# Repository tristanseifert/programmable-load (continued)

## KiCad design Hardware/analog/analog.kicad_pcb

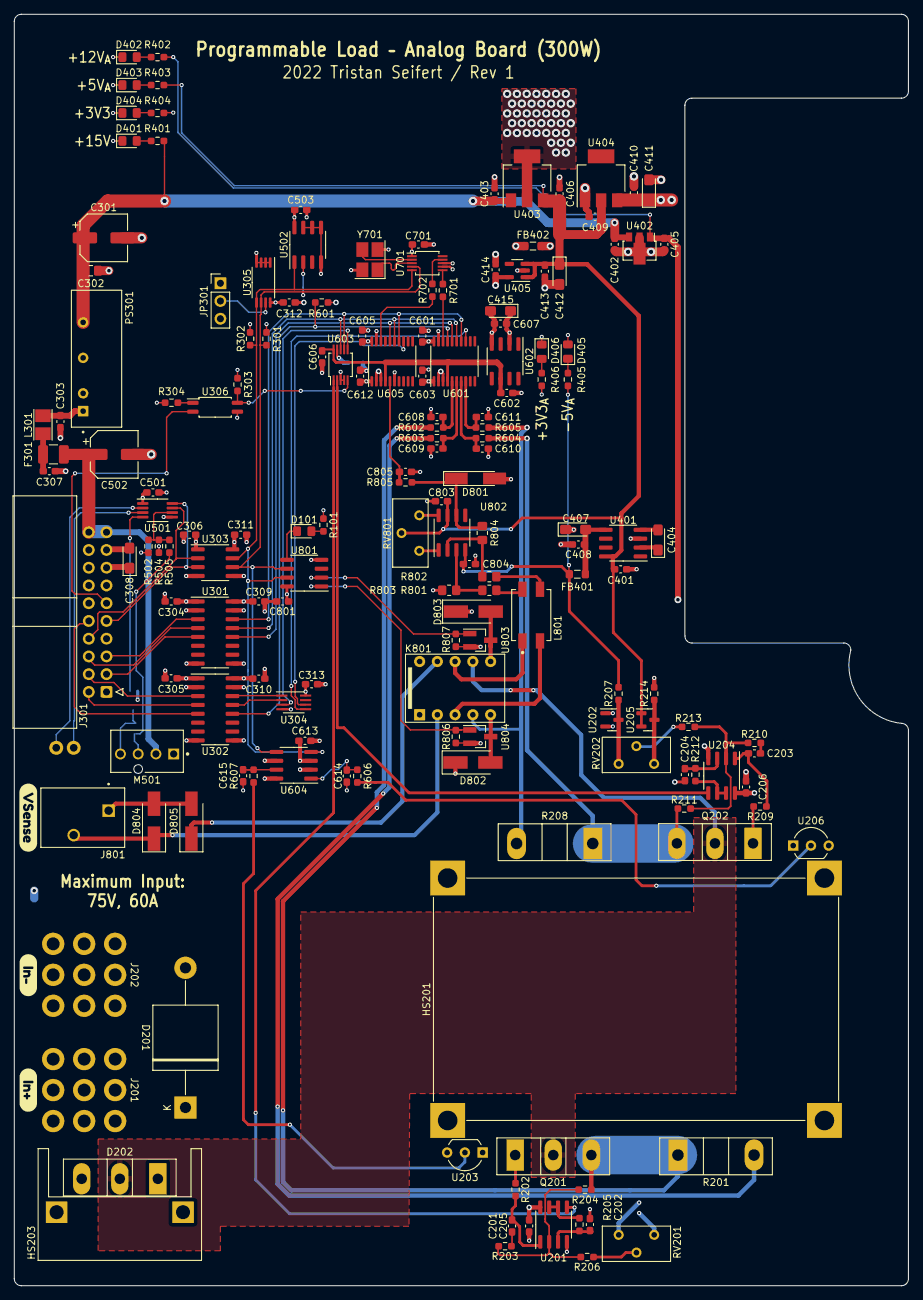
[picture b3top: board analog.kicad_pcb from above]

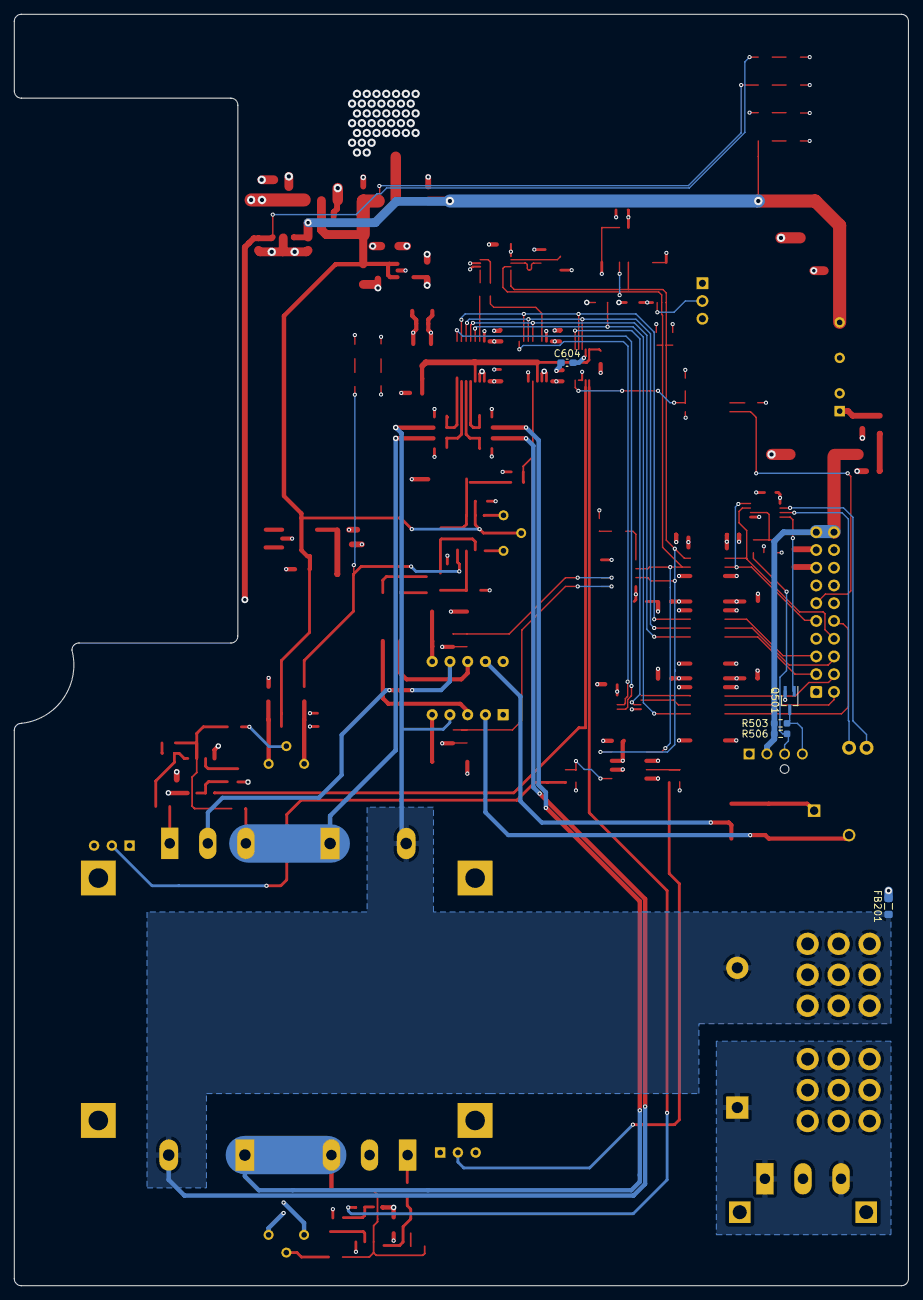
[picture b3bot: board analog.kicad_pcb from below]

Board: 4 copper layers, 128.0 x 182.0 mm, 174 parts (5 on the bottom side), 108 nets.

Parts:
C201, C203: 1nF; C_0603_1608Metric_Pad1.08x0.95mm_HandSolder
C202, C204: 22nF; C_0603_1608Metric_Pad1.08x0.95mm_HandSolder
C205, C206, C304, C305, C306, C309, C310, C311, C312, C313, C408, C501, C503, C601, C603, C604, C605, C607, C608, C609, C610, C611, C612, C613, C614, C615, C701, C801, C803, C804, C805: 100nF; C_0603_1608Metric_Pad1.08x0.95mm_HandSolder
C301, C502: 33µF; CP_Elec_6.3x5.7
C302: 10µF; C_0805_2012Metric_Pad1.18x1.45mm_HandSolder
C303, C307, C401, C402, C403, C405, C406, C409, C410, C413, C414, C602, C606: 4.7µF; C_0603_1608Metric_Pad1.08x0.95mm_HandSolder
C308, C404, C407, C411, C412, C415: 10µF; CP_EIA-3216-18_Kemet-A_Pad1.58x1.35mm_HandSolder
D101: Red; LED_0805_2012Metric_Pad1.15x1.40mm_HandSolder
D201: 5KP78A; D_P600_R-6_P20.00mm_Horizontal
D202: DSA120C150QB; TO-247-3_Vertical
D401, D402, D403, D404, D405, D406: Green; LED_0805_2012Metric_Pad1.15x1.40mm_HandSolder
D801: 2V4; D_MiniMELF_Handsoldering
D802, D803: SM4007; D_SMA_Handsoldering
D804: 75V; D_SMA_Handsoldering
D805: SS110; D_SMA_Handsoldering
F301: 350mA; Fuse_1210_3225Metric_Pad1.42x2.65mm_HandSolder
FB201, FB401, FB402: FerriteBead_Small; L_0805_2012Metric_Pad1.05x1.20mm_HandSolder
HS201: 2x C40-058-AE; C40-058-AE-DUAL
HS203: WV-T247-101E; Ohmite-WA-T247-101E-MFG
J201, J202: Würth 74651194R; WE-74651194
J301: Conn_02x10_Odd_Even; IDC-Header_2x10_P2.54mm_Horizontal
J501, J502: Conn_01x01; MillMax-2108-2
J801: Conn_01x02; CUI_TBL002A-350-02GR-2OR
JP301: Cfg WP; PinHeader_1x03_P2.54mm_Vertical
K801: EA2-3T; KEMET-EA2
L301: 6.8µH; L_Taiyo-Yuden_NR-24xx_HandSoldering
L801: L_Ferrite_Coupled_1423; Bourns-DR331-0-0-MFG
M501: Fan_4pin; Molex-47053-1000-MFG
PS301: PCN2-S12-S15-S; CONV_PCN2-S12-S15-S
Q201, Q202: IXTH80N075L2; TO-247-3_Vertical
Q501: MMBT3904; SOT-323_SC-70_Handsoldering
R101, R203, R204, R207, R210, R211, R214, R404, R406, R602, R603, R604, R605: 1k; R_0603_1608Metric_Pad0.98x0.95mm_HandSolder
R201, R208: .05R; TO-247-2_Vertical
R202, R209: 100R; R_0603_1608Metric_Pad0.98x0.95mm_HandSolder
R205, R212, R402, R805: 4k99; R_0603_1608Metric_Pad0.98x0.95mm_HandSolder
R206, R213: 330k (?); R_0603_1608Metric_Pad0.98x0.95mm_HandSolder
R301, R302, R403, R405: 2k2; R_0603_1608Metric_Pad0.98x0.95mm_HandSolder
R303, R504, R601: 10k; R_0603_1608Metric_Pad0.98x0.95mm_HandSolder
R304: 200R; R_0603_1608Metric_Pad0.98x0.95mm_HandSolder
R401: 7k5; R_0603_1608Metric_Pad0.98x0.95mm_HandSolder
R502: 5k6; R_0603_1608Metric_Pad0.98x0.95mm_HandSolder
R503, R506, R806, R807: 4k7; R_0603_1608Metric_Pad0.98x0.95mm_HandSolder
R505: 27k4; R_0603_1608Metric_Pad0.98x0.95mm_HandSolder
R606, R607: 27k1; R_0603_1608Metric_Pad0.98x0.95mm_HandSolder
R701, R702: 0R; R_0603_1608Metric_Pad0.98x0.95mm_HandSolder
R801, R802: 1M .1%; R_0805_2012Metric_Pad1.20x1.40mm_HandSolder
R803, R804: 20k .1%; R_0805_2012Metric_Pad1.20x1.40mm_HandSolder
RV201, RV202: 10k; Potentiometer_Nidec_Copal_CT94EY
RV801: 20k; Potentiometer_Nidec_Copal_CT94EY
U201, U204: ADA4522-2; SOIC-8_3.9x4.9mm_P1.27mm
U202, U205: LM431SC; SOT-23
U203, U206: LMT86LMT; TO-92_Inline_Wide
U301, U302: ADUM131D; SOIC-16_3.9x9.9mm_P1.27mm
U303: ADUM1250; SOIC-8_3.9x4.9mm_P1.27mm
U304: 74LVC1G139; SSOP-8_2.95x2.8mm_P0.65mm
U305: AT24CS32-SSHM; TSSOP-8_4.4x3mm_P0.65mm
U306: FODM217B; SOP-4_4.4x2.6mm_P1.27mm
U401: ICL7660; SOIC-8_3.9x4.9mm_P1.27mm
U402: MCP1804x-C002xMB; SOT-89-3
U403: MCP1703AT-5002E/DB; SOT-223-3_TabPin2
U404: XC6203E33; SOT-223
U405: LP5907MFX-3.3; SOT-23-5
U501: EMC2101-R; MSOP-8_3x3mm_P0.65mm
U502: LM75B; SOIC-8_3.9x4.9mm_P1.27mm
U601: MCP3562; TSSOP-20_4.4x6.5mm_P0.65mm
U602: MAX6166; SOIC-8_3.9x4.9mm_P1.27mm
U603: DAC8562; MSOP-10_3x3mm_P0.5mm
U604: MCP3426-xSN; SOIC-8_3.9x4.9mm_P1.27mm
U605: MCP3561; TSSOP-20_4.4x6.5mm_P0.65mm
U701: Si5351A-B-GT; MSOP-10_3x3mm_P0.5mm
U801: PCA9536D; SOIC-8_3.9x4.9mm_P1.27mm
U802: OPA277; SOIC-8_3.9x4.9mm_P1.27mm
U803, U804: MMBT3904; SOT-23_Handsoldering
Y701: 25MHz; Crystal_SMD_SeikoEpson_TSX3225-4Pin_3.2x2.5mm_HandSoldering
kibuzzard-6291C153: G***; kibuzzard-6291C153
kibuzzard-6280396F: G***; kibuzzard-6280396F
kibuzzard-62803980: G***; kibuzzard-62803980

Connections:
+3.3VP: C304.1, C305.1, C306.1, C308.1, C501.1, J301.15, J301.16, R304.2, R502.1, U301.1 (VCC_{1}), U302.1 (VCC_{1}), U303.1 (VDD1), U501.1 (VCC)
+3V3: C309.1, C310.1, C311.1, C312.1, C313.1, C410.1, C411.1, C503.1, C601.1, C605.1, C613.1, C701.1, C801.1, D802.1 (K), D803.1 (K), JP301.3 (B), K801.1, K801.10, R101.1, R301.2, R302.2, R303.1, R404.1, R601.2, U203.1 (Vdd), U206.1 (Vdd), U301.16 (VCC_{2}), U302.16 (VCC_{2}), U303.8 (VDD2), U304.8 (VCC), U305.8 (VCC), U404.3 (V_{out}), U502.8 (+Vs), U601.20 (D_{VCC}), U604.3 (VDD), U605.20 (D_{VCC}), U701.1 (VDD), U701.7 (VDDO), U801.8 (VDD)
+3V3A: C414.1, C415.1, C603.1, C604.1, C607.1, C612.1, R406.1, U405.5 (OUT), U601.1 (A_{VCC}), U602.2 (V_{in}), U603.9 (A_{VDD}), U605.1 (A_{VCC})
+5VA: C401.1, C406.1, C409.1, C412.1, C413.1, C803.1, R403.1, RV801.2, U205.1 (K), U205.2 (REF), U401.8 (V+), U403.3 (VO), U404.2 (V_{in}), U405.1 (IN), U405.3 (EN), U802.7 (V+)
+12VA: C205.2, C206.2, C405.1, R402.1, U201.8 (V+), U204.8 (V+), U402.1 (OUT)
+15V: C301.1, C302.1, C402.1, C403.1, PS301.6 (+Vout), R401.1, U402.3 (IN), U403.1 (VI)
+VDC: D202.2 (A), K801.7, Q201.2 (D), Q202.2 (D)
-5VA: C804.1, FB401.2, R207.2, R405.1, U802.4 (V-)
/Analog stuff/ADCCLK_{0}: R701.2, U601.18 (MCLK)
/Analog stuff/ADCCLK_{1}: R702.2, U605.18 (MCLK)
/Analog stuff/SPI_MISO: U301.12 (I_{C), U601.16 (MISO), U605.16 (MISO)
/Analog stuff/SPI_MOSI: U301.13 (O_{B), U601.15 (MOSI), U603.8 (MOSI), U605.15 (MOSI)
/Analog stuff/SPI_SCK: U301.14 (O_{A), U601.14 (SCK), U603.7 (SCLK), U605.14 (SCK)
/Analog stuff/Sense_{0+}: C608.1, R602.2, U601.5 (CH0)
/Analog stuff/Sense_{0-}: C609.2, R603.2, U601.6 (CH1)
/Analog stuff/Sense_{1+}: C610.1, R604.2, U601.7 (CH2)
/Analog stuff/Sense_{1-}: C611.2, R605.2, U601.8 (CH3)
/Analog stuff/TempSense_{0}: C614.1, R606.1, U604.1 (CH1+)
/Analog stuff/TempSense_{1}: C615.1, R607.1, U604.7 (CH2+)
/Analog stuff/VREF: C602.1, C606.1, U601.4 (REFIN+), U602.6 (V_{out}), U603.10 (VRef), U605.4 (REFIN+)
/Analog stuff/~CS_ADC_{0}: U304.5 (Y2), U601.13 (~CS)
/Analog stuff/~CS_ADC_{1}: U304.6 (Y1), U605.13 (~CS)
/Analog stuff/~CS_DAC: U304.3 (Y3), U603.6 (~SYNC)
/Analog stuff/~IRQ: R601.1, U302.12 (I_{C), U601.17 (~IRQ/MDAT)
/External Interface/IN_SPI_MOSI: J301.6, U301.4 (I_{B)
/External Interface/IN_SPI_SCK: J301.5, U301.3 (I_{A)
/External Interface/IN_SPI_SSEL0: J301.4, U302.3 (I_{A)
/External Interface/IN_SPI_SSEL1: J301.2, U302.4 (I_{B)
/External Interface/OUT_SPI_MISO: J301.3, U301.5 (O_{C)
/External Interface/SEL_0: U302.14 (O_{A), U304.1 (A)
/External Interface/SEL_1: U302.13 (O_{B), U304.2 (B)
/External Interface/~IN_RESET: J301.11, U306.2
/External Interface/~OUT_IRQ: J301.10, U302.5 (O_{C)
/External Interface/~RESET: R303.2, U306.4, U603.5 (~CLR)
/Fan Control & Temperature Sensors/FAN_PWM: Q501.1 (B), U501.4 (FAN)
/Fan Control & Temperature Sensors/FAN_TACH: R502.2, R504.2, R505.2, U501.6 (TACH)
/Fan Control & Temperature Sensors/TEMP_DN: J502.1, U501.3 (DN)
/Fan Control & Temperature Sensors/TEMP_DP: J501.1, U501.2 (DP)
/I2C_SCL: R301.1, U303.6 (SCL2), U305.6 (SCL), U502.2 (SCL), U604.5 (SCL), U701.4 (SCL), U801.6 (SCL)
/I2C_SDA: R302.1, U303.7 (SDA2), U305.5 (SDA), U502.1 (SDA), U604.4 (SDA), U701.5 (SDA), U801.7 (SDA)
/ISense_{0}: Q201.3 (S), R201.1, R204.2, R602.1
/ISense_{1}: Q202.3 (S), R208.1, R211.2, R604.1
/ISet_{0}: U201.5 (+), U603.1 (VOUT_{A})
/ISet_{1}: U204.5 (+), U603.2 (VOUT_{B})
/LED_STATUS: D101.1 (K), U801.5 (IO3)
/MOSFET Load/OffRef+: R214.1, RV201.3, RV202.3, U205.3 (A)
/MOSFET Load/OffRef-: R207.1, RV201.1, RV202.1, U202.3 (A)
/MOSFET Load/VBUS_IN: D201.1 (A1), D202.1 (K), D202.3 (K), J201.1
/TEMP_{0}: R606.2, U206.2 (OUT)
/TEMP_{1}: R607.2, U203.2 (OUT)
/VSense: C805.1, R805.1, U605.5 (CH0)
/Voltage Sense/EXT_SENSE+: D805.1 (K), K801.9
/Voltage Sense/EXT_SENSE-: D804.1 (A1), J801.2, K801.2
/Voltage Sense/IO_RLY_RESET: R807.2, U801.2 (IO1), U803.1 (B)
/Voltage Sense/IO_RLY_SET: R806.2, U801.1 (IO0), U804.1 (B)
/Voltage Sense/RELAY_RESET: D803.2 (A), K801.6, U803.3 (C)
/Voltage Sense/RELAY_SET: D802.2 (A), K801.5, U804.3 (C)
/Voltage Sense/VIN+: L801.4, R801.1
/Voltage Sense/VIN-: L801.3, R802.2
GND: C202.2, C204.2, C205.1, C206.1, C301.2, C302.2, C309.2, C310.2, C311.2, C312.2, C313.2, C401.2, C402.2, C403.2, C405.2, C406.2, C407.1, C408.2, C409.2, C410.2, C411.2, C412.2, C413.2, C503.2, C601.2, C605.2, C608.2, C609.1, C610.2, C611.1, C613.2, C614.2, C615.2, C701.2, C801.2, C803.2, C804.2, C805.2, D401.1 (K), D402.1 (K), D403.1 (K), D404.1 (K), D405.2 (A), D801.2 (A), FB201.2, FB402.1, JP301.1 (A), PS301.4 (-Vout), R214.2, R803.2, R806.1, R807.1, U201.4 (V-), U202.1 (K), U202.2 (REF), U203.3 (GND), U204.4 (V-), U206.3 (GND), U301.9 (GND_{2}), U301.15 (GND_{2}), U302.9 (GND_{2}), U302.15 (GND_{2}), U303.5 (GND2), U304.4 (GND), U305.1 (A0), U305.2 (A1), U305.3 (A2), U305.4 (GND), U306.3, U401.3 (GND), U402.2 (GND), U403.2 (GND), U404.1 (GND), U502.4 (GND), U502.5 (A2), U502.6 (A1), U502.7 (A0), U601.19 (D_{GND}), U604.2 (CH1-), U604.6 (VSS), U604.8 (CH2-), U605.19 (D_{GND}), U701.8 (GND), U801.4 (VSS), U803.2 (E), U804.2 (E), Y701.2, Y701.4
GND2: C303.2, C304.2, C305.2, C306.2, C307.2, C308.2, C501.2, C502.2, J301.7, J301.13, J301.14, J301.17, J301.18, M501.1 (-), PS301.2 (-Vin), Q501.2 (E), R504.1, U301.2 (GND_{1}), U301.8 (GND_{1}), U302.2 (GND_{1}), U302.8 (GND_{1}), U303.4 (GND1), U501.5 (GND)
GNDA: C414.2, C415.2, C602.2, C603.2, C604.2, C606.2, C607.2, C612.2, D406.1 (K), FB402.2, U405.2 (GND), U601.2 (A_{GND}), U601.3 (REFIN-), U602.4 (GND), U603.3 (GND), U603.4 (~{LDAC), U605.2 (A_{GND}), U605.3 (REFIN-), U605.6 (CH1)
GNDPWR: D201.2 (A2), FB201.1, J202.1, K801.4, R201.2, R208.2, R603.1, R605.1
IN_I2C_SCL: J301.9, U303.3 (SCL1), U501.8 (SMCLK)
IN_I2C_SDA: J301.8, U303.2 (SDA1), U501.7 (SMDATA)
unnamed: C201.1, R202.2, U201.1
unnamed: C201.2, R203.1
unnamed: C203.1, R209.2, U204.1
unnamed: C203.2, R210.1
unnamed: C307.1, F301.1, L301.2
unnamed: D101.2 (A), R101.2
unnamed: D401.2 (A), R401.2
unnamed: D402.2 (A), R402.2
unnamed: D403.2 (A), R403.2
unnamed: D404.2 (A), R404.2
unnamed: D405.1 (K), R405.2
unnamed: D406.2 (A), R406.2
unnamed: D801.1 (K), R804.1, R805.2, U802.6
unnamed: D804.2 (A2), D805.2 (A), J801.1
unnamed: JP301.2 (C), U305.7 (WP)
unnamed: K801.3, L801.2
unnamed: K801.8, L801.1
unnamed: M501.4 (PWM), Q501.3 (C), R503.1
unnamed: M501.3 (Tacho), R505.1, R506.1
unnamed: C303.1, L301.1, PS301.1 (+Vin)
unnamed: Q201.1 (G), R202.1
unnamed: Q202.1 (G), R209.1
unnamed: R206.1, RV201.2
unnamed: R213.1, RV202.2
unnamed: R304.1, U306.1
unnamed: C202.1, R205.1, U201.3 (+)
unnamed: R203.2, R204.1, R206.2, U201.2 (-)
unnamed: R205.2, U201.6 (-), U201.7
unnamed: C204.1, R212.1, U204.3 (+)
unnamed: R210.2, R211.1, R213.2, U204.2 (-)
unnamed: R212.2, U204.6 (-), U204.7
unnamed: C404.1, U401.2 (CAP+)
unnamed: C404.2, U401.4 (CAP-)
unnamed: C407.2, C408.1, FB401.1, U401.5 (VOUT)
unnamed: R702.1, U701.9 (CLK1)
unnamed: R701.1, U701.6 (CLK2)
unnamed: U701.2 (XA), Y701.3
unnamed: U701.3 (XB), Y701.1
unnamed: R801.2, R803.1, U802.3 (+)
unnamed: R802.1, R804.2, U802.2 (-)
unnamed: RV801.1, U802.1 (T)
unnamed: RV801.3, U802.8 (T)
VBUS: C502.1, F301.2, J301.19, J301.20, M501.2 (+), R503.2, R506.2

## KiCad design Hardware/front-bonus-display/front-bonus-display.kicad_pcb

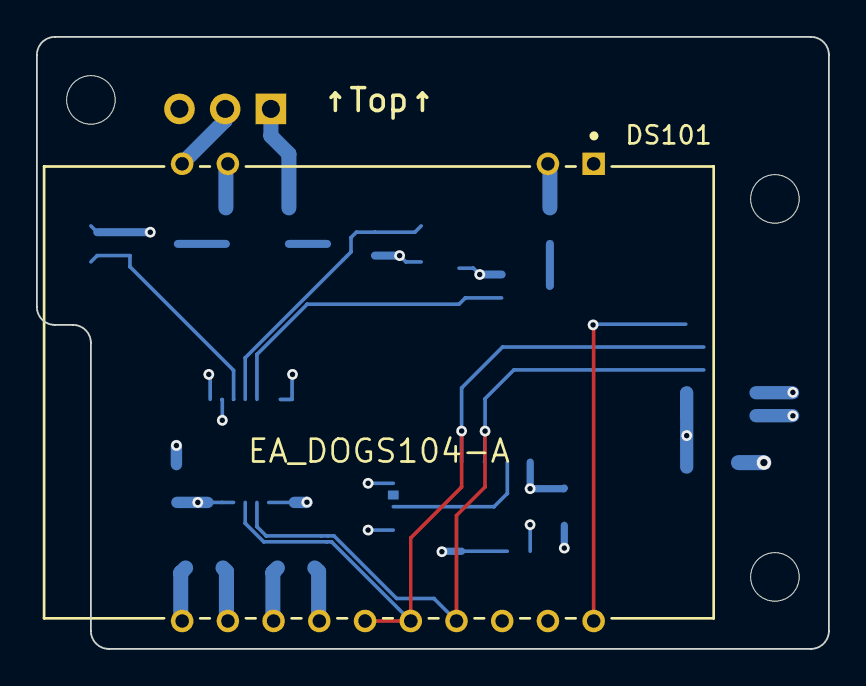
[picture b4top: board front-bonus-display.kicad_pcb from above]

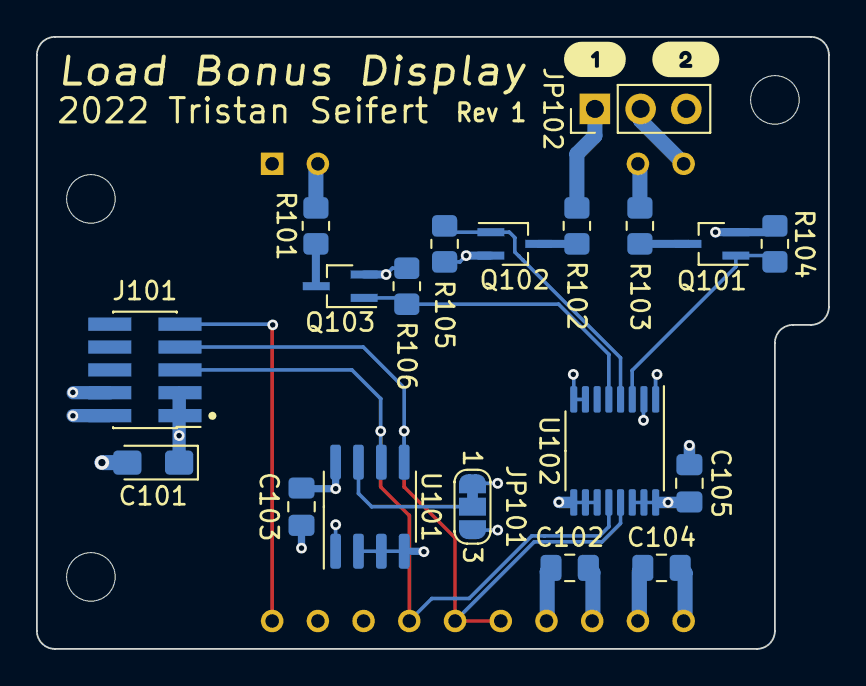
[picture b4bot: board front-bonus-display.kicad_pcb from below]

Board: 4 copper layers, 44.0 x 34.0 mm, 25 parts (21 on the bottom side), 17 nets.

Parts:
C101: 10µF; CP_EIA-3216-18_Kemet-A_Pad1.58x1.35mm_HandSolder
C102, C104: 1µF; C_0805_2012Metric_Pad1.18x1.45mm_HandSolder
C103, C105: 100nF; C_0805_2012Metric_Pad1.18x1.45mm_HandSolder
DS101: EA_DOGS104-A; Display_Visions-EA_DOGS104-A-BACKLIGHT-SOCKET
H101, H102, H104: MountingHole; MountingHole_2.7mm_M2.5
J101: Conn_02x05_Odd_Even; PinHeader_2x05_P1.27mm_Vertical_SMD
JP101: Cfg WP; SolderJumper-3_P1.3mm_Bridged12_RoundedPad1.0x1.5mm_NumberL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
JP102: Jumper_3_Open; PinHeader_1x03_P2.54mm_Vertical
Q101, Q102, Q103: MMBT3904; SOT-323_SC-70_Handsoldering
R101: 27R; R_0805_2012Metric_Pad1.20x1.40mm_HandSolder
R102: 10R; R_0805_2012Metric_Pad1.20x1.40mm_HandSolder
R103: 20R; R_0805_2012Metric_Pad1.20x1.40mm_HandSolder
R104, R105, R106: 10k; R_0805_2012Metric_Pad1.20x1.40mm_HandSolder
U101: AT24CS32-SSHM; SOIC-8_3.9x4.9mm_P1.27mm
U102: PCA9633; TSSOP-16_4.4x5mm_P0.65mm
kibuzzard-627F235A: G***; kibuzzard-627F235A
kibuzzard-627F2330: G***; kibuzzard-627F2330

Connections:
+3V3: C101.1, C102.1, C103.1, C105.1, DS101.1 (A1/AGR/AERW), DS101.13 (VDD), J101.1, J101.3, JP101.3 (B), JP102.3, U101.1 (A0), U101.8 (VCC), U102.1 (A0), U102.14 (A5), U102.15 (A6), U102.16 (VCC)
/I2C_SCL: DS101.17 (SCLK), J101.5, U101.6 (SCL), U102.12 (SCL)
/I2C_SDA: DS101.15 (SOD), DS101.16 (SID), J101.7, U101.5 (SDA), U102.13 (SDA)
/LED_C1: Q103.3 (C), R101.1
/LED_C2: Q102.3 (C), R102.1
/LED_C3: Q101.3 (C), R103.1
/~RESET: DS101.20 (~RESET), J101.9
GND: C101.2, C102.2, C103.2, C104.2, C105.2, DS101.12 (IM1), DS101.14 (GND), DS101.18 (~CS), DS101.19 (SA0), J101.2, J101.4, JP101.1 (A), Q101.2 (E), Q102.2 (E), Q103.2 (E), R104.1, R105.1, R106.1, U101.2 (A1), U101.3 (A2), U101.4 (GND), U102.2 (A1), U102.7 (A2), U102.8 (A3), U102.9 (GND), U102.10 (~OE), U102.11 (A4)
unnamed: C104.1, DS101.11 (VOUT)
unnamed: DS101.2 (C1/CR/CR), R101.2
unnamed: DS101.9 (C2/CG/CE), R103.2
unnamed: DS101.10 (A2/NC/CW), JP102.2
unnamed: JP101.2 (C), U101.7 (WP)
unnamed: JP102.1, R102.2
unnamed: Q101.1 (B), R104.2, U102.3 (LED0)
unnamed: Q102.1 (B), R105.2, U102.4 (LED1)
unnamed: Q103.1 (B), R106.2, U102.5 (LED2)

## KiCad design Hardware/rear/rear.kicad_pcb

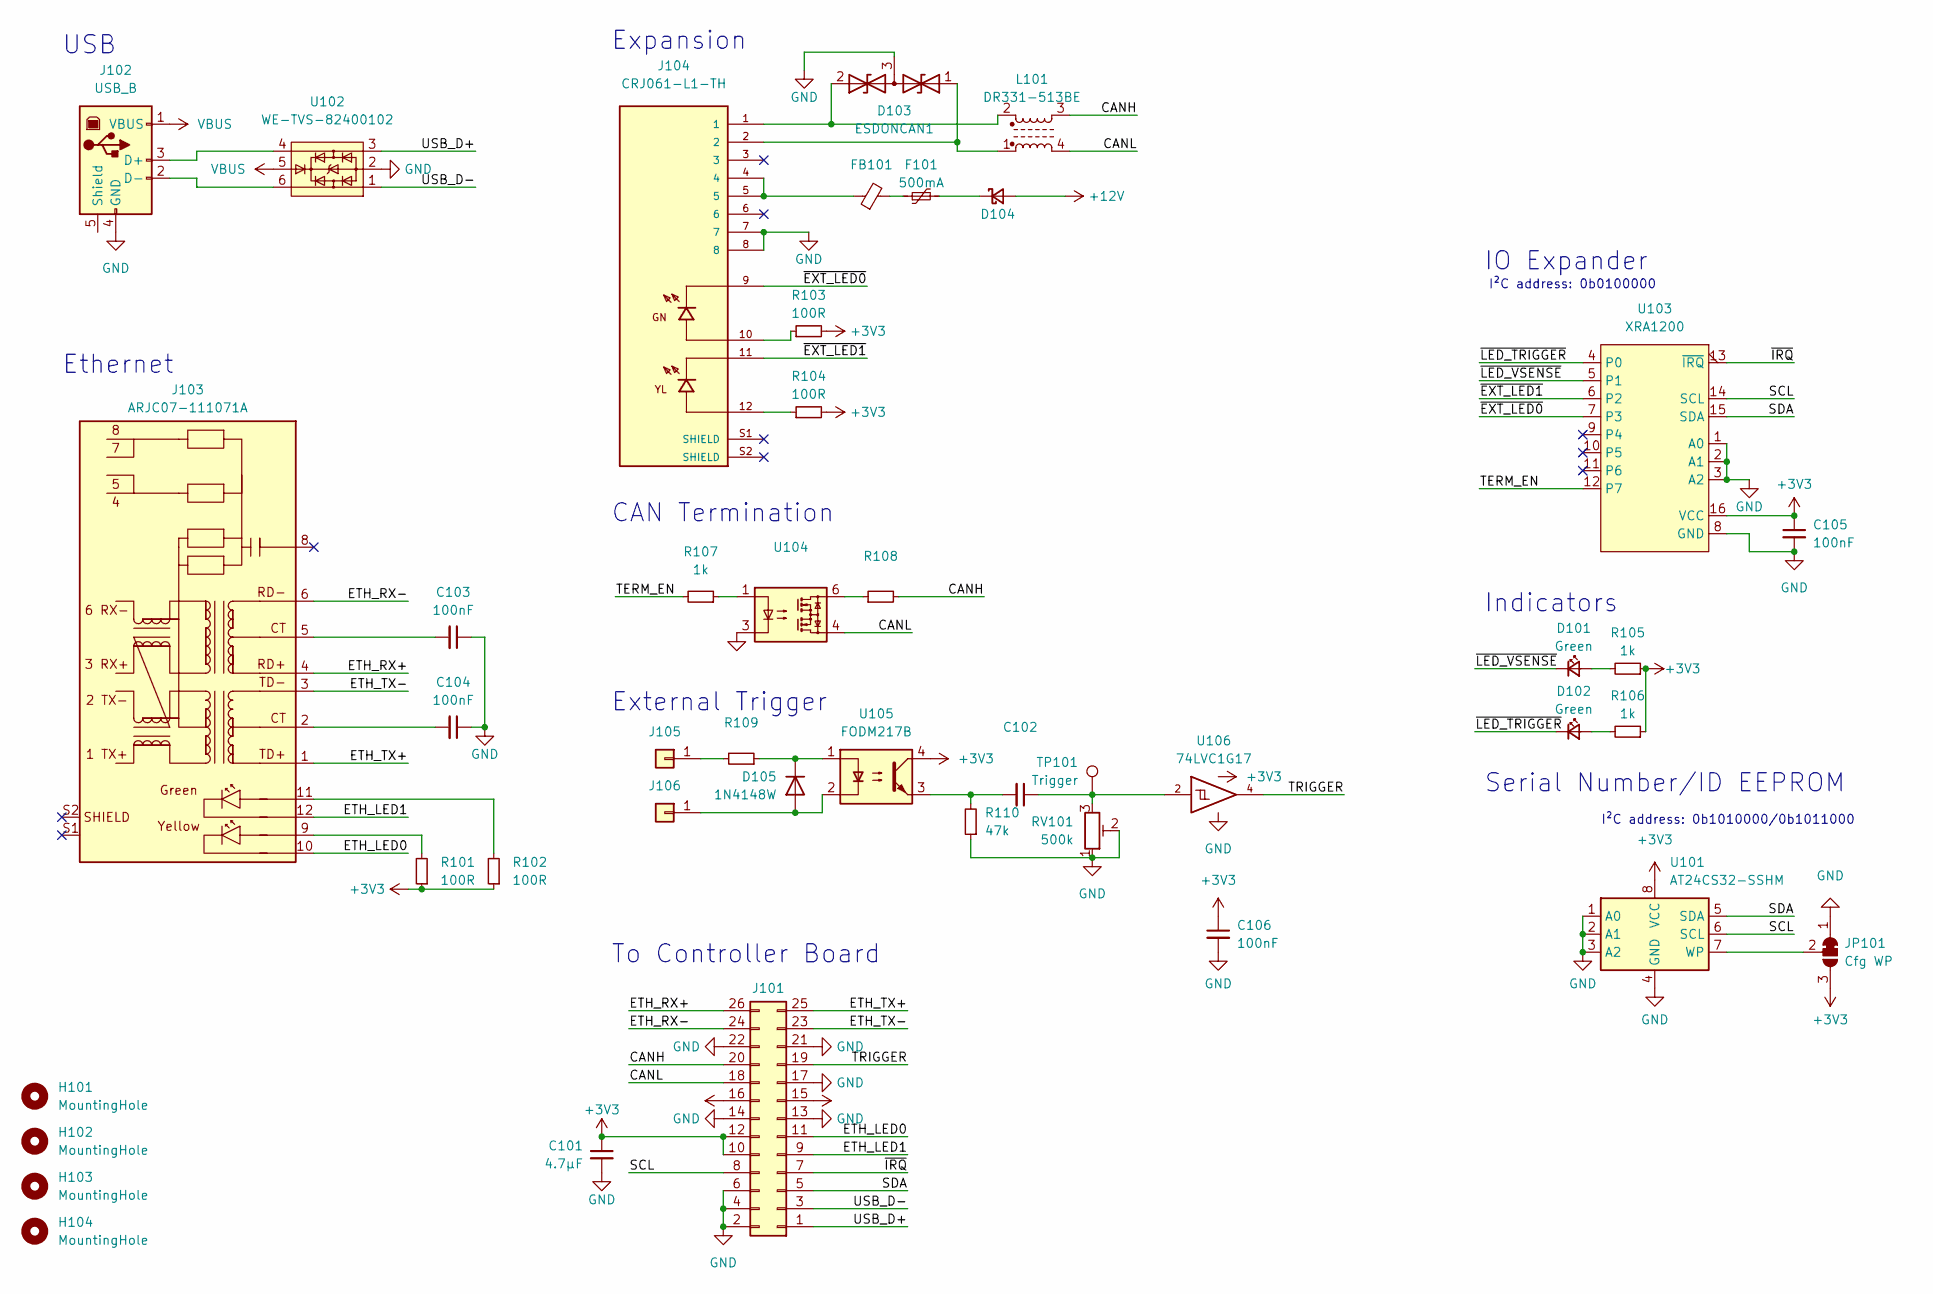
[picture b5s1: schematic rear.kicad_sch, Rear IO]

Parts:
C101: 4.7µF; C_0805_2012Metric_Pad1.18x1.45mm_HandSolder; MPN CL21A475KAQNNNF
C102: MPN CL21B105KBFNNNG
C103, C104, C105: 100nF; C_0805_2012Metric_Pad1.18x1.45mm_HandSolder; MPN CL21B104KACNFNC
C106: 100nF; C_0805_2012Metric_Pad1.18x1.45mm_HandSolder
D101, D102: Green; LED_0805_2012Metric_Pad1.15x1.40mm_HandSolder
D103: ESDONCAN1; SOT-23_Handsoldering; MPN ESDONCAN1LT1G
D104: Panjit SS14; D_SMA_Handsoldering; MPN SS14_R1_00001
D105: 1N4148W; D_SOD-123; MPN 1N4148W-AU_R1_000A1
F101: 500mA; Fuse_1206_3216Metric_Pad1.42x1.75mm_HandSolder; MPN 0ZCJ0050FF2G
FB101: FerriteBead_Small; L_0805_2012Metric_Pad1.05x1.20mm_HandSolder; MPN MFBM1V2012-800-R
H101, H102, H103, H104: MountingHole; MountingHole_2.7mm_M2.5
J101: Conn_02x10_Odd_Even; PinHeader_2x13_P1.27mm_Vertical; MPN 20021111-00026T4LF
J102: USB_B; USB_B_TE_5787834_Vertical_ShieldSplit; MPN 5787834-2
J103: ARJC07-111071A; ABRACON-ARJC07-111071A; MPN ARJC07-111071A
J104: CRJ061-L1-TH; CUI_CRJ061-L1-TH; PARTREV 1.0
J105: MPN 2108-2-00-01-00-00-07-0
J106: Conn_01x01; MillMax-2108-2; MPN 2108-2-00-01-00-00-07-0
JP101: Cfg WP; SolderJumper-3_P1.3mm_Bridged12_RoundedPad1.0x1.5mm
L101: DR331-513BE; Bourns-DR331-0-0-MFG; MPN DR331-513BE
R101, R102, R103, R104: 100R; R_0805_2012Metric_Pad1.20x1.40mm_HandSolder; MPN WR08X101 JTL
R105, R106, R107: 1k; R_0805_2012Metric_Pad1.20x1.40mm_HandSolder; MPN CR0805-JW-102ELF
R108: MPN RMC1/4-101JTE
R109: MPN 260-200-RC
R110: 47k; R_0805_2012Metric_Pad1.20x1.40mm_HandSolder; MPN RMC1/10-473JTP
RV101: 500k; Potentiometer_Nidec_Copal_CT94EW; MPN CT-94EW504
TP101: Trigger; TestPoint_Keystone_5000-5004_Miniature; MPN 5004
U101: AT24CS32-SSHM; SOIC-8_3.9x4.9mm_P1.27mm; MPN AT24CS32-SSHM
U102: WE-TVS-82400102; SOT-23-6; MPN 82400102
U103: XRA1200; TSSOP-16_4.4x5mm_P0.65mm
U104: (no value)
U105: FODM217B; SOP-4_4.4x2.6mm_P1.27mm; MPN FODM217B
U106: 74LVC1G17; SOT-23-5_HandSoldering; MPN SN74LVC1G17DBVRG4

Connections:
+3V3: C101.1, C105.1, C106.1, J101.10, J101.12, JP101.3 (B), R101.1, R102.1, R103.2, R104.2, R105.1, R106.1, U101.8 (VCC), U103.16 (VCC), U105.4, U106.5 (VCC)
/CANH: J101.20, L101.3, R108.2
/CANL: J101.18, L101.4, U104.4
/ETH_LED0: J101.11, J103.10 (RLED-)
/ETH_LED1: J101.9, J103.12 (LLED-)
/ETH_RX+: J101.26, J103.4 (RD+)
/ETH_RX-: J101.24, J103.6 (RD-)
/ETH_TX+: J101.25, J103.1 (TD+)
/ETH_TX-: J101.23, J103.3 (TD-)
/SCL: J101.8, U101.6 (SCL), U103.14 (SCL)
/SDA: J101.5, U101.5 (SDA), U103.15 (SDA)
/TERM_EN: R107.2, U103.12 (P7)
/TRIGGER: J101.19, U106.4
/USB_D+: J101.1, U102.3
/USB_D-: J101.3, U102.1
/~EXT_LED0: J104.9, U103.7 (P3)
/~EXT_LED1: J104.11, U103.6 (P2)
/~IRQ: J101.7, U103.13 (~IRQ)
/~LED_TRIGGER: D102.1 (K), U103.4 (P0)
/~LED_VSENSE: D101.1 (K), U103.5 (P1)
unnamed: C102.1, RV101.3, TP101.1, U106.2
unnamed: C103.2, J103.5 (CT)
unnamed: C104.2, J103.2 (CT)
unnamed: D101.2 (A), R105.2
unnamed: D102.2 (A), R106.2
unnamed: D103.1 (A1), J104.2, L101.1
unnamed: D103.2 (A2), J104.1, L101.2
unnamed: D104.1 (K), F101.2
unnamed: D105.1 (K), R109.1, U105.1
unnamed: F101.1, FB101.2
unnamed: FB101.1, J104.4, J104.5
unnamed: J102.2 (D-), U102.6
unnamed: J102.3 (D+), U102.4
unnamed: J103.9 (RLED+), R101.2
unnamed: J103.11 (LLED+), R102.2
unnamed: J104.10, R103.1
unnamed: J104.12, R104.1
unnamed: J105.1, R109.2
unnamed: D105.2 (A), J106.1, U105.2
unnamed: JP101.2 (C), U101.7 (WP)
unnamed: R107.1, U104.1
unnamed: R108.1, U104.6
unnamed: C102.2, R110.2, U105.3
VBUS: J102.1 (VBUS), U102.5

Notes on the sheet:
IO Expander
USB
Ethernet
I²C address: 0b1010000/0b1011000
External Trigger
To Controller Board
CAN Termination
Indicators
Expansion
I²C address: 0b0100000
Serial Number/ID EEPROM

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
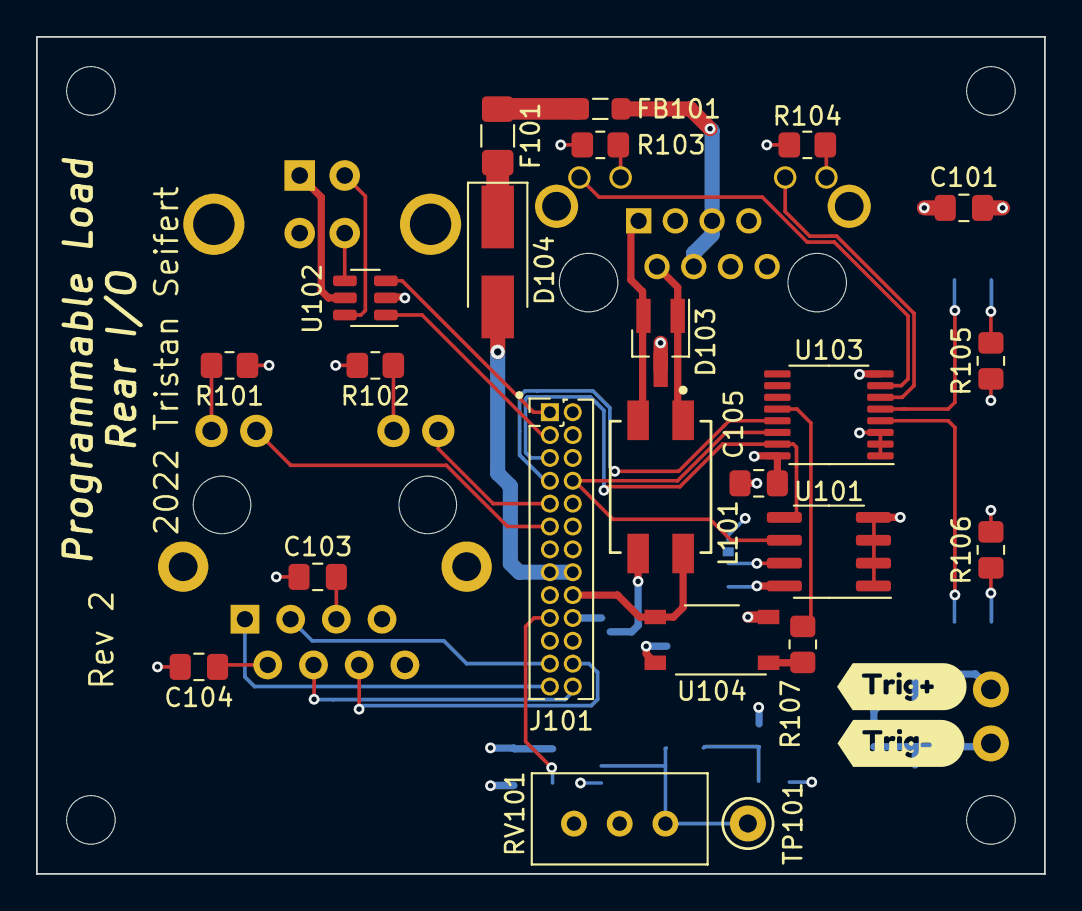
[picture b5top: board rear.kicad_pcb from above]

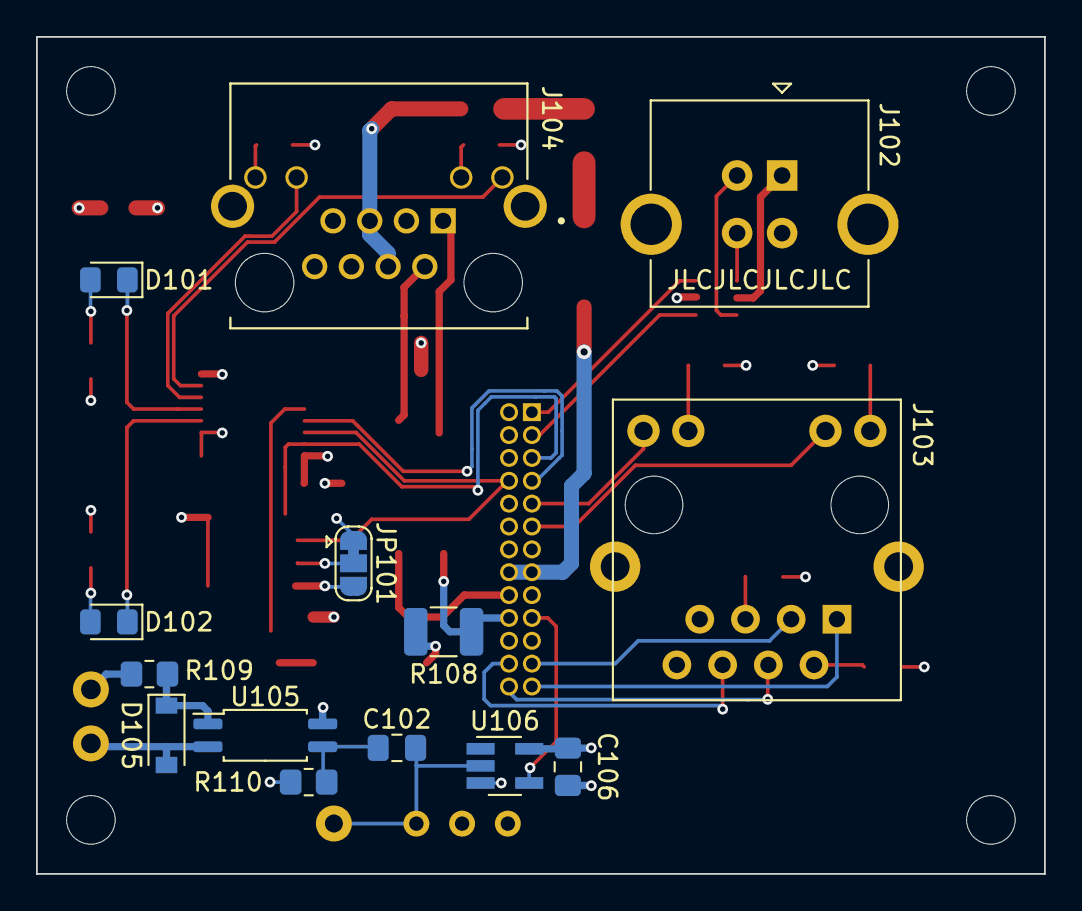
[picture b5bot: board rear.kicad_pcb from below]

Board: 4 copper layers, 56.0 x 46.5 mm, 45 parts (14 on the bottom side), 46 nets.

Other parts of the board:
kibuzzard-62664110: G***; kibuzzard-62664110
kibuzzard-62664123: G***; kibuzzard-62664123

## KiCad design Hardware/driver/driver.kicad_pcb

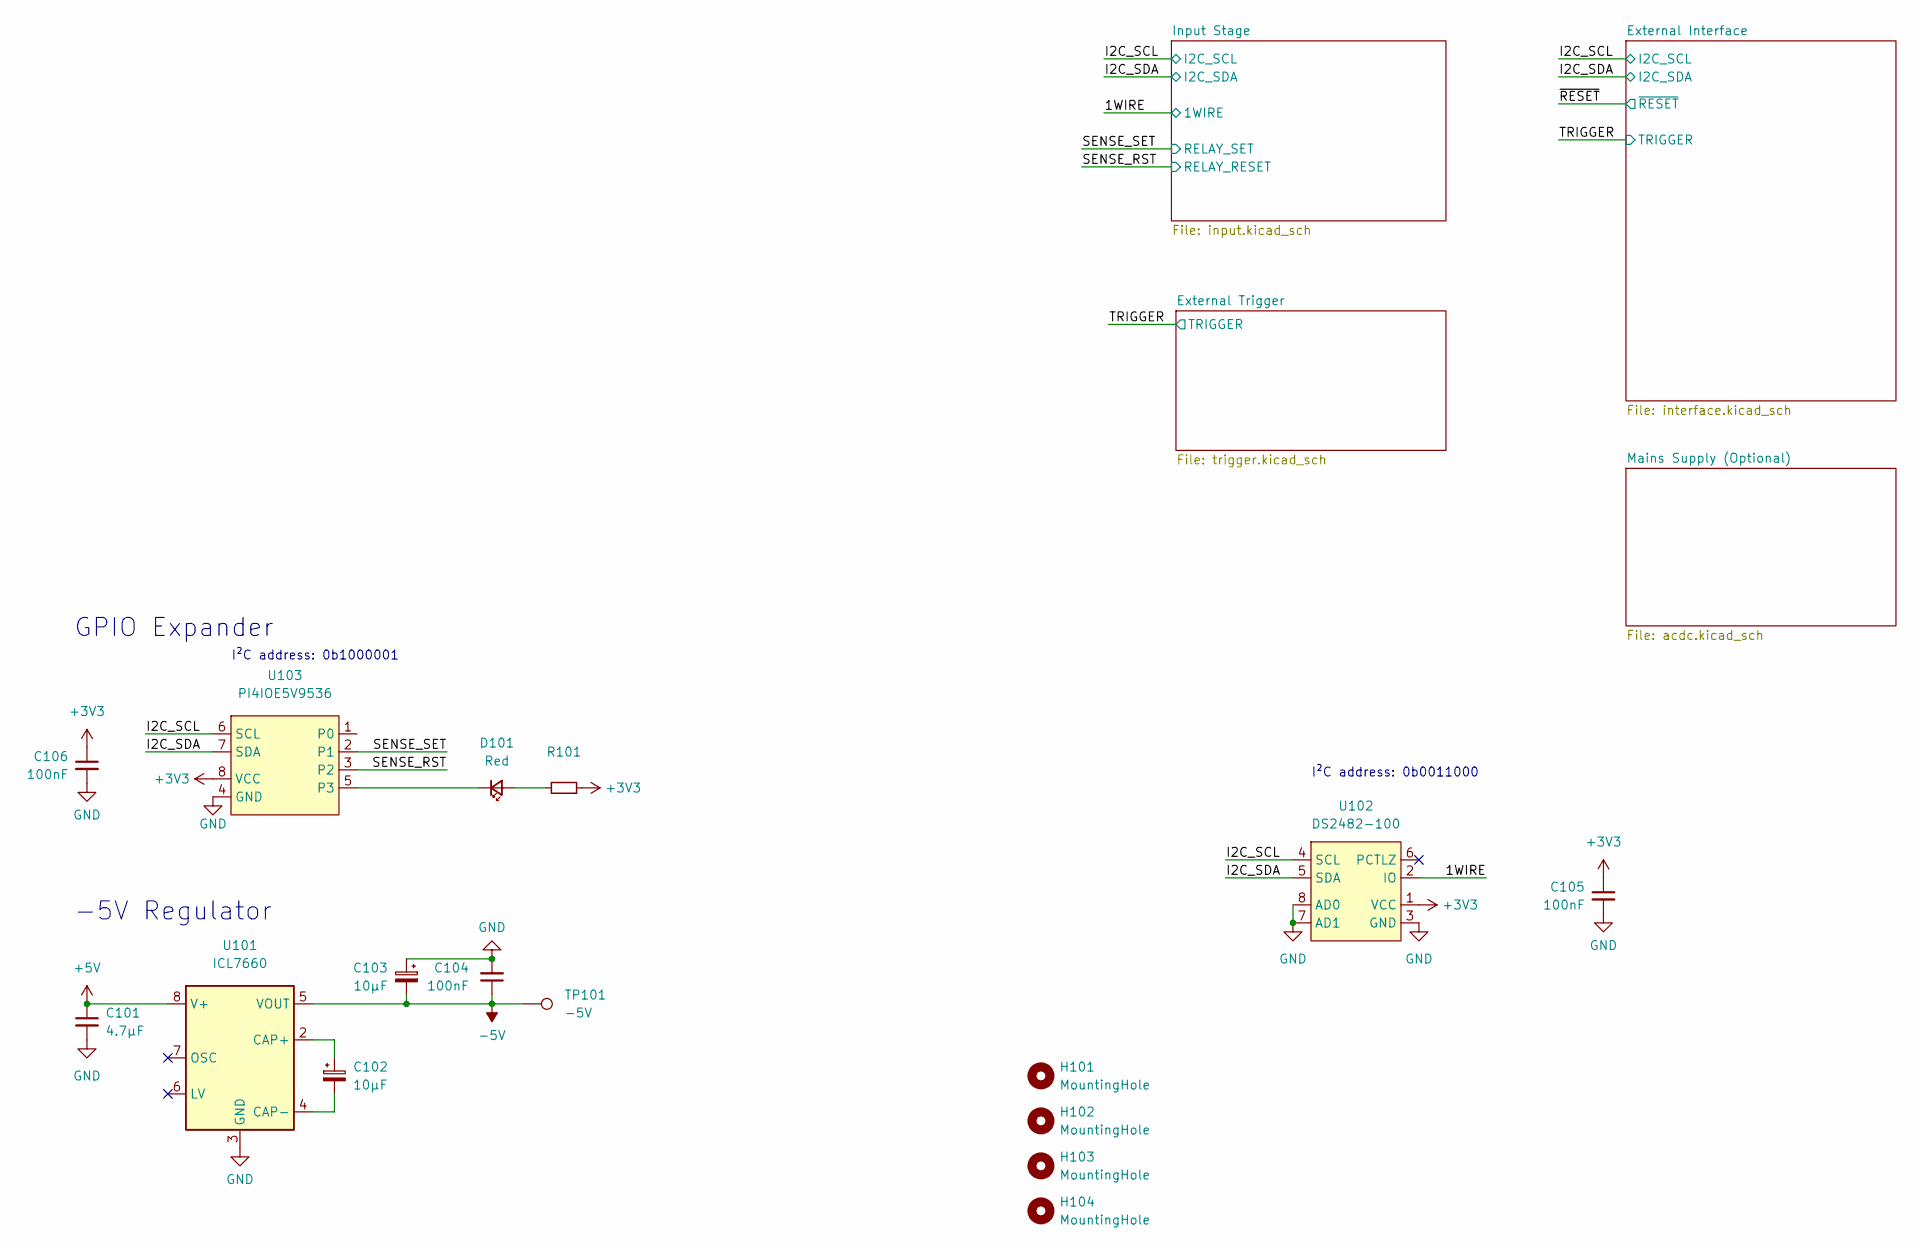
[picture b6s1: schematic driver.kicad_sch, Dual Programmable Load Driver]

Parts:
C101: 4.7µF; C_0805_2012Metric_Pad1.18x1.45mm_HandSolder; MPN CL21A475KAQNNNF
C102, C103: 10µF; CP_EIA-3216-18_Kemet-A_Pad1.58x1.35mm_HandSolder; MPN TAJA106K016RNJ
C104, C105, C106: 100nF; C_0805_2012Metric_Pad1.18x1.45mm_HandSolder
D101: Red; LED_0805_2012Metric_Pad1.15x1.40mm_HandSolder; MPN 150080SS75000
H101, H102, H103, H104: MountingHole; MountingHole_3.5mm
R101: MPN CR0805-JW-102ELF
TP101: -5V; TestPoint_Keystone_5000-5004_Miniature; MPN 5000
U101: ICL7660; SOIC-8_3.9x4.9mm_P1.27mm; MPN ICL7660CSA+T
U102: DS2482-100; SO-8_3.9x4.9mm_P1.27mm
U103: PI4IOE5V9536; MSOP-8_3x3mm_P0.65mm; MPN PI4IOE5V9536UEX

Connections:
+3V3: C105.1, C106.1, R101.1, U102.1 (VCC), U103.8 (VCC); also elsewhere on the board
+5V: C101.1, U101.8 (V+); also elsewhere on the board
-5V: C103.2, C104.1, TP101.1, U101.5 (VOUT); also elsewhere on the board
/1WIRE: U102.2 (IO); also elsewhere on the board
/I2C_SCL: U102.4 (SCL), U103.6 (SCL); also elsewhere on the board
/I2C_SDA: U102.5 (SDA), U103.7 (SDA); also elsewhere on the board
/SENSE_RST: U103.3 (P2); also elsewhere on the board
/SENSE_SET: U103.2 (P1); also elsewhere on the board
GND: C101.2, C103.1, C104.2, C105.2, C106.2, U101.3 (GND), U102.3 (GND), U102.7 (AD1), U102.8 (AD0), U103.4 (GND); also elsewhere on the board
unnamed: C102.1, U101.2 (CAP+)
unnamed: C102.2, U101.4 (CAP-)
unnamed: D101.1 (K), U103.5 (P3)
unnamed: D101.2 (A), R101.2

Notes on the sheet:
-5V Regulator
I²C address: 0b1000001
GPIO Expander
I²C address: 0b0011000
